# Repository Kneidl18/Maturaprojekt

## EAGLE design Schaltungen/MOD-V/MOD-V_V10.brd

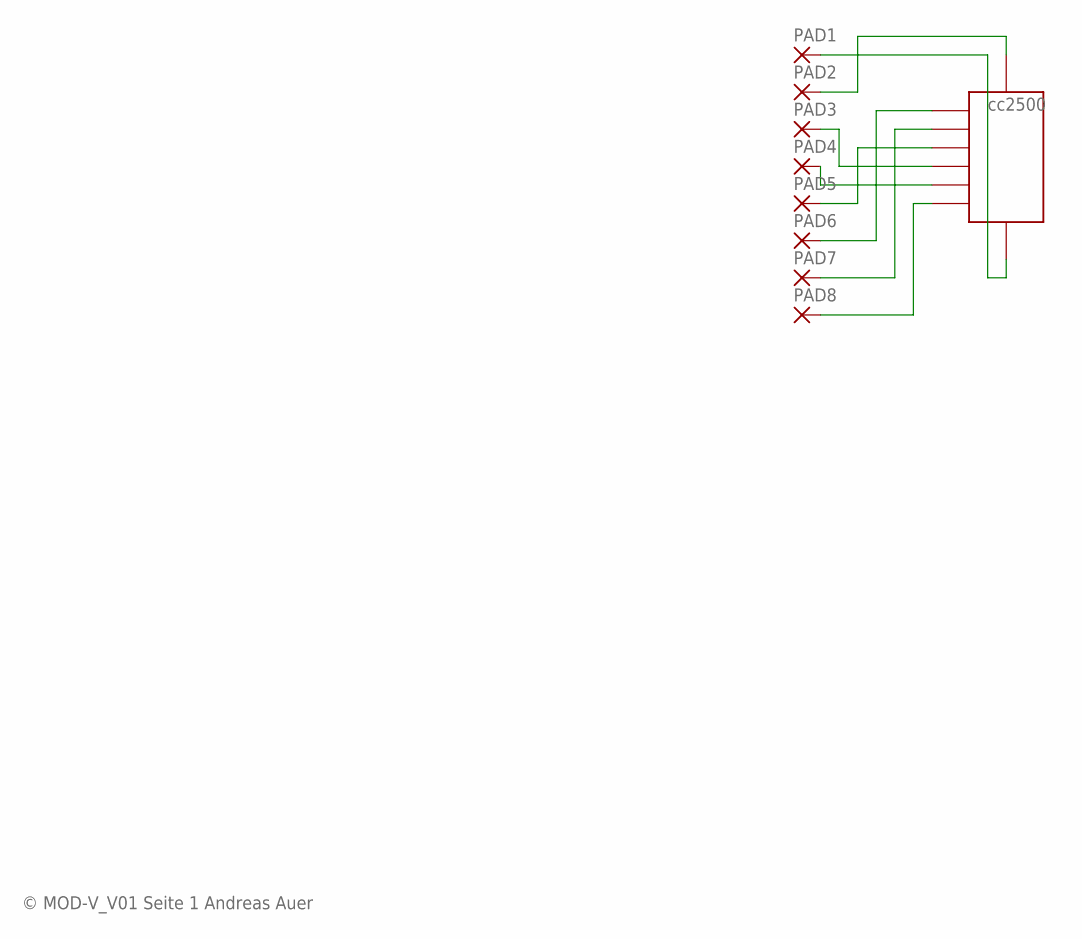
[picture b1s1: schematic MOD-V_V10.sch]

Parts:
IC1: CC2500
PAD1, PAD2, PAD3, PAD4, PAD5, PAD6, PAD7, PAD8: SMD2; SMD1,27-2,54

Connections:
unnamed: IC1.GND, PAD1.1
unnamed: IC1.+3V3, PAD2.1
unnamed: IC1.SPSCK, PAD4.1
unnamed: IC1.MISO, PAD5.1
unnamed: IC1.GD2, PAD7.1
unnamed: IC1.CS, PAD8.1
unnamed: IC1.MOSI, PAD3.1
unnamed: IC1.GD0, PAD6.1

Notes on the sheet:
© MOD-V_V01 Seite 1 Andreas Auer

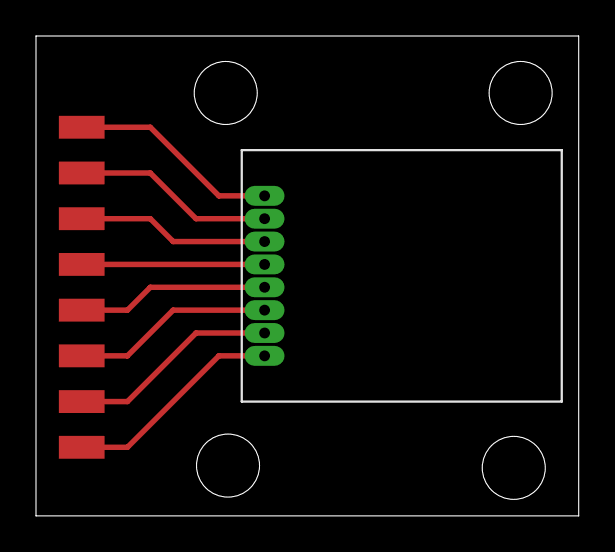
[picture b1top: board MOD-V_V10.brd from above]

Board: 2 copper layers, 30.1 x 26.7 mm, 9 parts (0 on the bottom side), 8 nets.

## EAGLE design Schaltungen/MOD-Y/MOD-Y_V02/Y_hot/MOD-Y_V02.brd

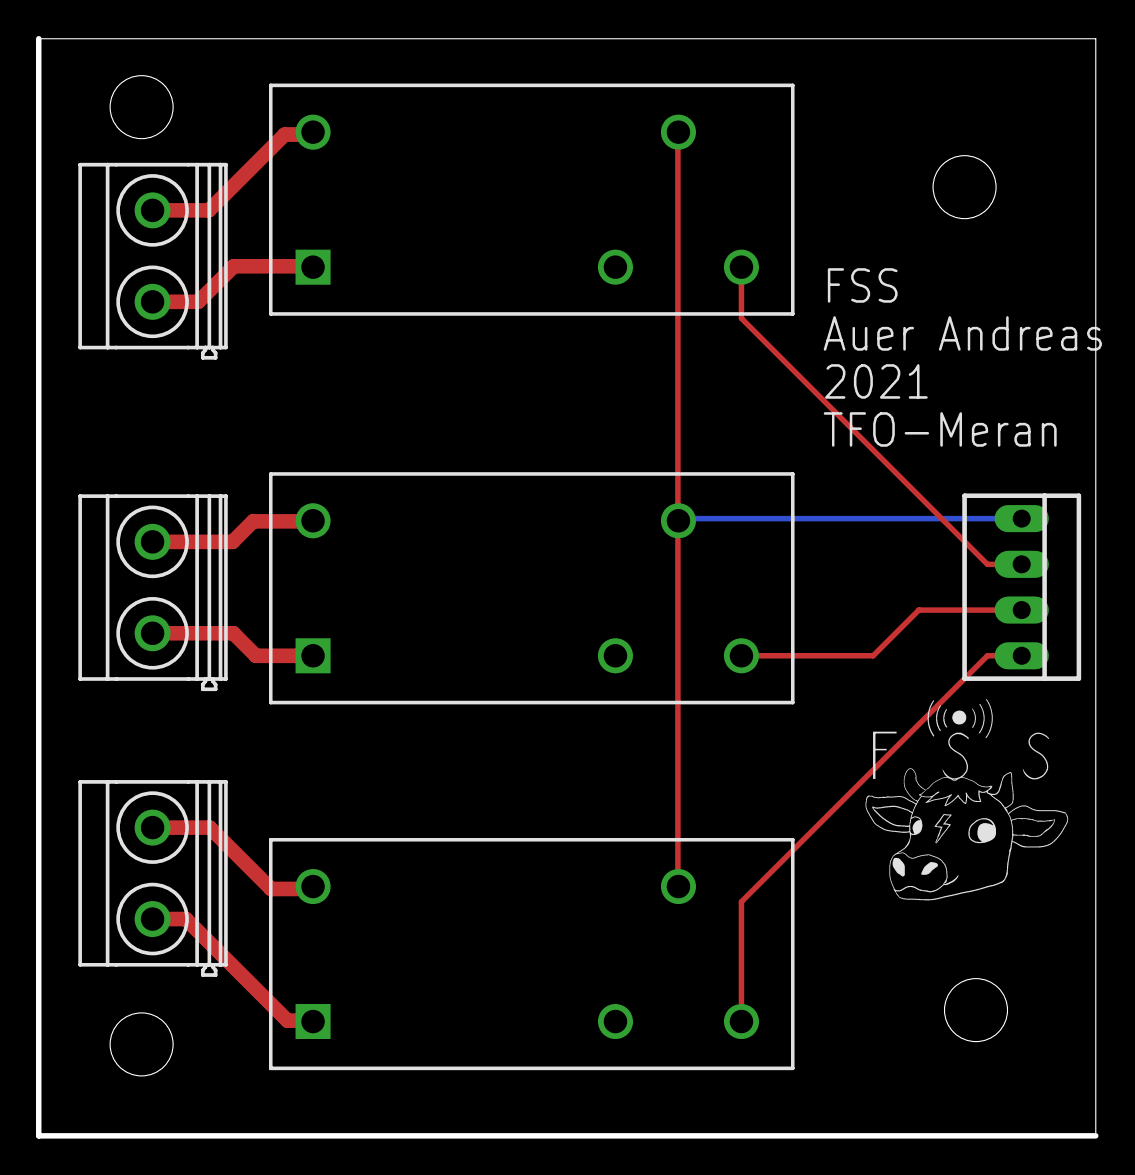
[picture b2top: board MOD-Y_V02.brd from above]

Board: 2 copper layers, 58.7 x 61.0 mm, 7 parts (0 on the bottom side), 10 nets.

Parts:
K7, K8, K9: RT14730
X1: 22-23-2041
X5, X6, X7: MKDSN1,5/2-5,08

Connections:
GND: K7.11, K8.11, K9.11, X1.1
unnamed: K7.A2, X5.2
unnamed: K9.A2, X7.2
unnamed: K8.A2, X6.2
unnamed: K7.A1, X5.1
unnamed: K8.A1, X6.1
unnamed: K9.A1, X7.1
NO1: K8.14, X1.2
NO2: K9.14, X1.3
NO3: K7.14, X1.4
